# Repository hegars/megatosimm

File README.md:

# megatosimm
 Arduino Mega 2560 to SIMM Adaptor

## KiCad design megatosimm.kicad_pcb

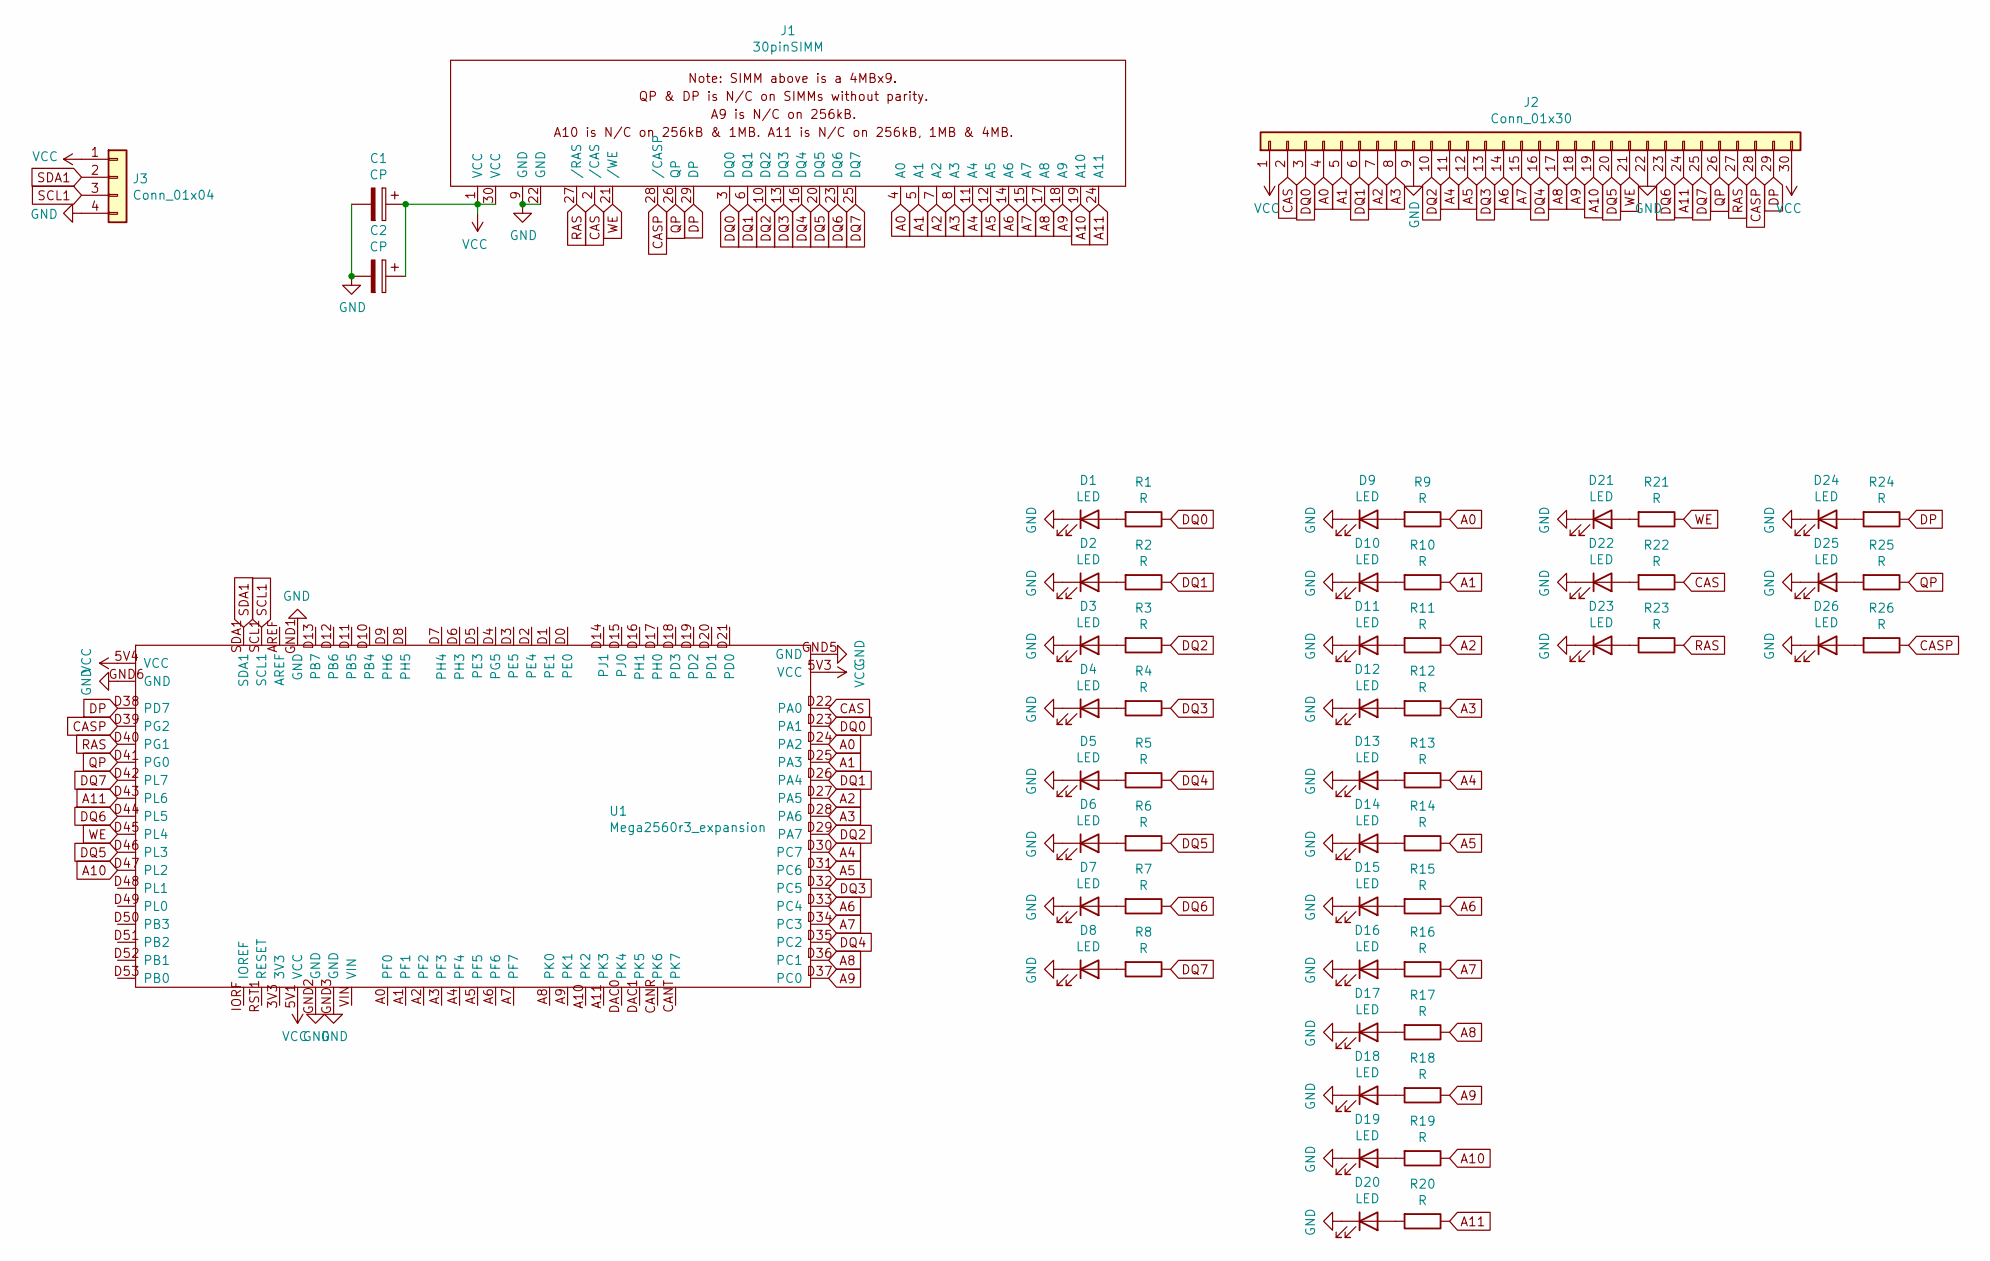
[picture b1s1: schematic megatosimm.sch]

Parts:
C1, C2: CP; CP_Radial_D4.0mm_P2.00mm
D1, D2, D3, D4, D5, D6, D7, D8, D9, D10, D11, D12, D13, D14, D15, D16, D17, D18, D19, D20, D21, D22, D23, D24, D25, D26: LED; LED_0805_HandSoldering
J1: 30pinSIMM; SIMM
J2: Conn_01x30; Pin_Header_Straight_1x30_Pitch2.54mm
J3: Conn_01x04; Pin_Header_Straight_1x04_Pitch2.54mm
R1, R2, R3, R4, R5, R6, R7, R8, R9, R10, R11, R12, R13, R14, R15, R16, R17, R18, R19, R20, R21, R22, R23, R24, R25, R26: R; R_0805_HandSoldering
U1: Mega2560r3_expansion; Arduino_Due_Shield

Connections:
A0: J1.4 (A0), J2.4, R9.1, U1.D24 (PA2)
A1: J1.5 (A1), J2.5, R10.1, U1.D25 (PA3)
A2: J1.7 (A2), J2.7, R11.1, U1.D27 (PA5)
A3: J1.8 (A3), J2.8, R12.1, U1.D28 (PA6)
A4: J1.11 (A4), J2.11, R13.1, U1.D30 (PC7)
A5: J1.12 (A5), J2.12, R14.1, U1.D31 (PC6)
A6: J1.14 (A6), J2.14, R15.1, U1.D33 (PC4)
A7: J1.15 (A7), J2.15, R16.1, U1.D34 (PC3)
A8: J1.17 (A8), J2.17, R17.1, U1.D36 (PC1)
A9: J1.18 (A9), J2.18, R18.1, U1.D37 (PC0)
A10: J1.19 (A10), J2.19, R19.1, U1.D47 (PL2)
A11: J1.24 (A11), J2.24, R20.1, U1.D43 (PL6)
CAS: J1.2 (/CAS), J2.2, R22.1, U1.D22 (PA0)
CASP: J1.28 (/CASP), J2.28, R26.1, U1.D39 (PG2)
DP: J1.29 (DP), J2.29, R24.1, U1.D38 (PD7)
DQ0: J1.3 (DQ0), J2.3, R1.1, U1.D23 (PA1)
DQ1: J1.6 (DQ1), J2.6, R2.1, U1.D26 (PA4)
DQ2: J1.10 (DQ2), J2.10, R3.1, U1.D29 (PA7)
DQ3: J1.13 (DQ3), J2.13, R4.1, U1.D32 (PC5)
DQ4: J1.16 (DQ4), J2.16, R5.1, U1.D35 (PC2)
DQ5: J1.20 (DQ5), J2.20, R6.1, U1.D46 (PL3)
DQ6: J1.23 (DQ6), J2.23, R7.1, U1.D44 (PL5)
DQ7: J1.25 (DQ7), J2.25, R8.1, U1.D42 (PL7)
GND: C1.2, C2.2, D1.1 (K), D2.1 (K), D3.1 (K), D4.1 (K), D5.1 (K), D6.1 (K), D7.1 (K), D8.1 (K), D9.1 (K), D10.1 (K), D11.1 (K), D12.1 (K), D13.1 (K), D14.1 (K), D15.1 (K), D16.1 (K), D17.1 (K), D18.1 (K), D19.1 (K), D20.1 (K), D21.1 (K), D22.1 (K), D23.1 (K), D24.1 (K), D25.1 (K), D26.1 (K), J1.9 (GND), J1.22 (GND), J2.9, J2.22, J3.4, U1.GND1 (GND), U1.GND2 (GND), U1.GND3 (GND), U1.GND5 (GND), U1.GND6 (GND)
unnamed: D1.2 (A), R1.2
unnamed: D2.2 (A), R2.2
unnamed: D3.2 (A), R3.2
unnamed: D4.2 (A), R4.2
unnamed: D5.2 (A), R5.2
unnamed: D6.2 (A), R6.2
unnamed: D7.2 (A), R7.2
unnamed: D8.2 (A), R8.2
unnamed: D9.2 (A), R9.2
unnamed: D10.2 (A), R10.2
unnamed: D11.2 (A), R11.2
unnamed: D12.2 (A), R12.2
unnamed: D13.2 (A), R13.2
unnamed: D14.2 (A), R14.2
unnamed: D15.2 (A), R15.2
unnamed: D16.2 (A), R16.2
unnamed: D17.2 (A), R17.2
unnamed: D18.2 (A), R18.2
unnamed: D19.2 (A), R19.2
unnamed: D20.2 (A), R20.2
unnamed: D21.2 (A), R21.2
unnamed: D22.2 (A), R22.2
unnamed: D23.2 (A), R23.2
unnamed: D24.2 (A), R24.2
unnamed: D25.2 (A), R25.2
unnamed: D26.2 (A), R26.2
QP: J1.26 (QP), J2.26, R25.1, U1.D41 (PG0)
RAS: J1.27 (/RAS), J2.27, R23.1, U1.D40 (PG1)
SCL1: J3.3, U1.SCL1
SDA1: J3.2, U1.SDA1
VCC: C1.1, C2.1, J1.1 (VCC), J1.30 (VCC), J2.1, J2.30, J3.1, U1.5V1 (VCC), U1.5V3 (VCC), U1.5V4 (VCC)
WE: J1.21 (/WE), J2.21, R21.1, U1.D45 (PL4)

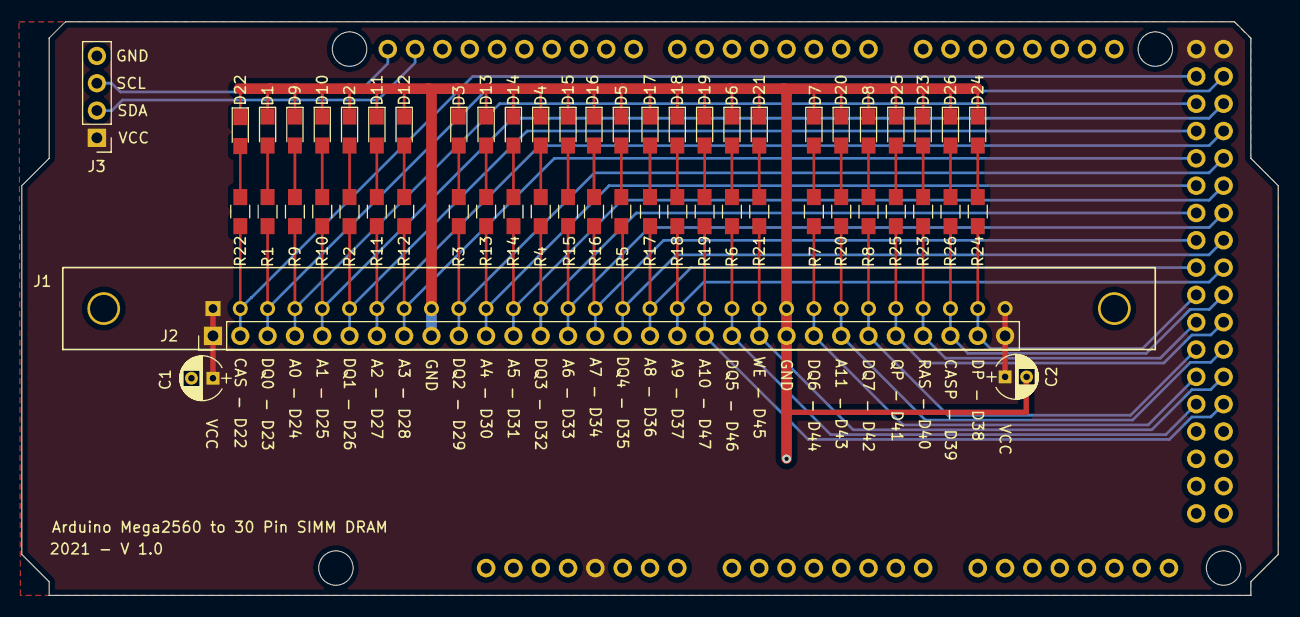
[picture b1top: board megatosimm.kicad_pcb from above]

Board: 2 copper layers, 116.8 x 53.3 mm, 58 parts (0 on the bottom side), 56 nets.

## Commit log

2021-02-27 added images
